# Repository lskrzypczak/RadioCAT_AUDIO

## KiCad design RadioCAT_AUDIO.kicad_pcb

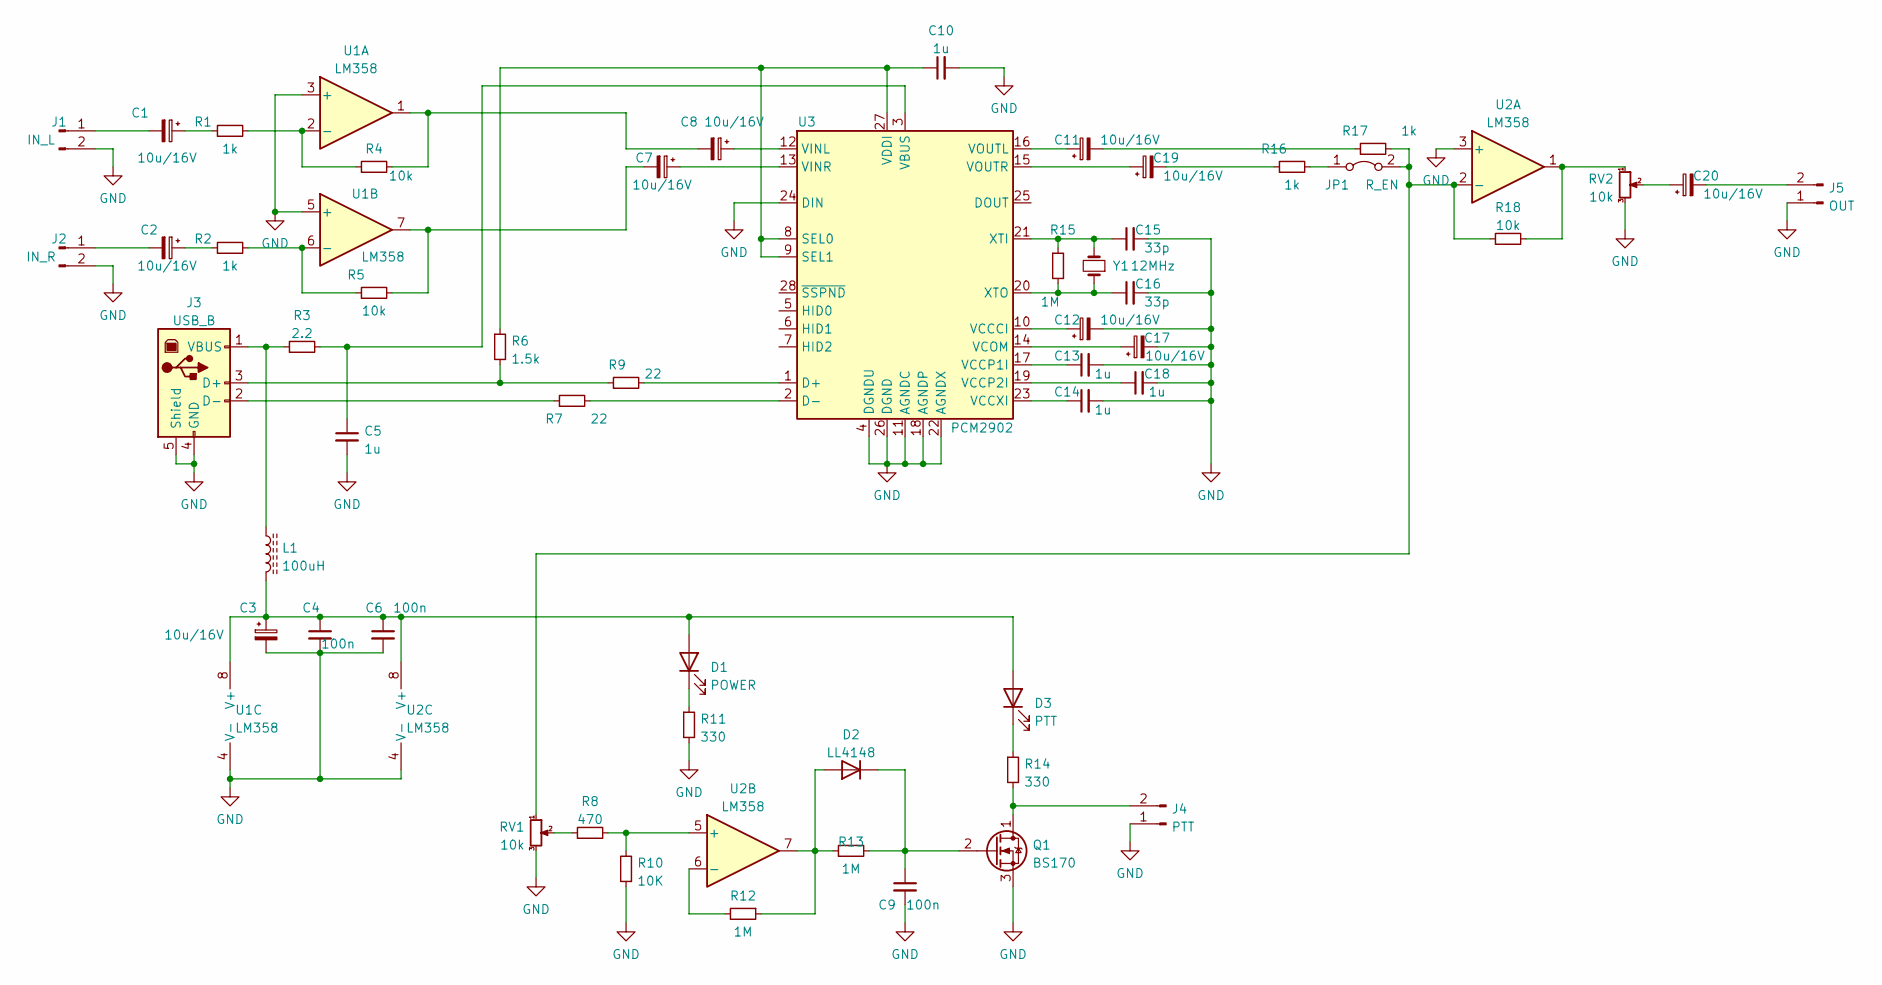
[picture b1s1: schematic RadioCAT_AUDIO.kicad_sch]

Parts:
C1, C2, C3, C7, C8, C11, C12, C17, C19, C20: 10u/16V; CP_Radial_D5.0mm_P2.50mm
C4, C6, C9: 100n; R_0805_2012Metric_Pad1.20x1.40mm_HandSolder
C5, C10, C13, C14, C18: 1u; R_0805_2012Metric_Pad1.20x1.40mm_HandSolder
C15, C16: 33p; R_0805_2012Metric_Pad1.20x1.40mm_HandSolder
D1: POWER; PinHeader_1x02_P2.54mm_Vertical
D2: LL4148; D_MiniMELF
D3: PTT; PinHeader_1x02_P2.54mm_Vertical
J1: IN_L; PinHeader_1x02_P2.54mm_Vertical
J2: IN_R; PinHeader_1x02_P2.54mm_Vertical
J3: USB_B; USB_B_Lumberg_2411_02_Horizontal
J4: PTT; PinHeader_1x02_P2.54mm_Vertical
J5: OUT; PinHeader_1x02_P2.54mm_Vertical
JP1: R_EN; PinHeader_1x02_P2.54mm_Vertical
L1: 100uH; L_7.3x7.3_H4.5
Q1: BS170; TO-92_Inline
R1, R2, R16, R17: 1k; R_0805_2012Metric_Pad1.20x1.40mm_HandSolder
R3: 2.2; R_0805_2012Metric_Pad1.20x1.40mm_HandSolder
R4, R5, R18: 10k; R_0805_2012Metric_Pad1.20x1.40mm_HandSolder
R6: 1.5k; R_0805_2012Metric_Pad1.20x1.40mm_HandSolder
R7, R9: 22; R_0805_2012Metric_Pad1.20x1.40mm_HandSolder
R8: 470; R_0805_2012Metric_Pad1.20x1.40mm_HandSolder
R10: 10K; R_0805_2012Metric_Pad1.20x1.40mm_HandSolder
R11, R14: 330; R_0805_2012Metric_Pad1.20x1.40mm_HandSolder
R12, R13, R15: 1M; R_0805_2012Metric_Pad1.20x1.40mm_HandSolder
RV1, RV2: 10k; PinHeader_1x03_P2.54mm_Vertical
U1, U2: LM358; SO-8_3.9x4.9mm_P1.27mm
U3: PCM2902; SSOP-28_5.3x10.2mm_P0.65mm
Y1: 12MHz; Crystal_HC49-4H_Vertical

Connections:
GND: C3.2, C4.2, C5.2, C6.2, C9.2, C10.2, C12.2, C13.2, C14.2, C15.2, C16.2, C17.2, C18.2, J1.2, J2.2, J3.4 (GND), J3.5 (Shield), J4.1, J5.1, Q1.3 (S), R10.1, R11.2, RV1.3, RV2.3, U1.3 (+), U1.4 (V-), U1.5 (+), U2.3 (+), U2.4 (V-), U3.4 (DGNDU), U3.11 (AGNDC), U3.18 (AGNDP), U3.22 (AGNDX), U3.24 (DIN), U3.26 (DGND)
unnamed: C1.1, R1.1
unnamed: C1.2, J1.1
unnamed: C2.1, R2.1
unnamed: C2.2, J2.1
unnamed: C3.1, C4.1, C6.1, D1.2 (A), D3.2 (A), L1.2, U1.8 (V+), U2.8 (V+)
unnamed: C5.1, R3.2, U3.3 (VBUS)
unnamed: C7.1, U3.13 (VINR)
unnamed: C7.2, R5.2, U1.7
unnamed: C8.1, U3.12 (VINL)
unnamed: C8.2, R4.2, U1.1
unnamed: C9.1, D2.1 (K), Q1.2 (G), R13.2
unnamed: C10.1, R6.1, U3.8 (SEL0), U3.9 (SEL1), U3.27 (VDDI)
unnamed: C11.1, U3.16 (VOUTL)
unnamed: C11.2, R17.1
unnamed: C12.1, U3.10 (VCCCI)
unnamed: C13.1, U3.17 (VCCP1I)
unnamed: C14.1, U3.23 (VCCXI)
unnamed: C15.1, R15.1, U3.21 (XTI), Y1.2
unnamed: C16.1, R15.2, U3.20 (XTO), Y1.1
unnamed: C17.1, U3.14 (VCOM)
unnamed: C18.1, U3.19 (VCCP2I)
unnamed: C19.1, U3.15 (VOUTR)
unnamed: C19.2, R16.1
unnamed: C20.1, RV2.2
unnamed: C20.2, J5.2
unnamed: D1.1 (K), R11.1
unnamed: D2.2 (A), R12.1, R13.1, U2.7
unnamed: D3.1 (K), R14.1
unnamed: J3.1 (VBUS), L1.1, R3.1
unnamed: J3.2 (D-), R7.1
unnamed: J3.3 (D+), R6.2, R9.1
unnamed: J4.2, Q1.1 (D), R14.2
unnamed: JP1.1 (A), R16.2
unnamed: JP1.2 (B), R17.2, R18.1, RV1.1, U2.2 (-)
unnamed: R1.2, R4.1, U1.2 (-)
unnamed: R2.2, R5.1, U1.6 (-)
unnamed: R7.2, U3.2 (D-)
unnamed: R8.1, RV1.2
unnamed: R9.2, U3.1 (D+)
unnamed: R8.2, R10.2, U2.5 (+)
unnamed: R12.2, U2.6 (-)
unnamed: R18.2, RV2.1, U2.1

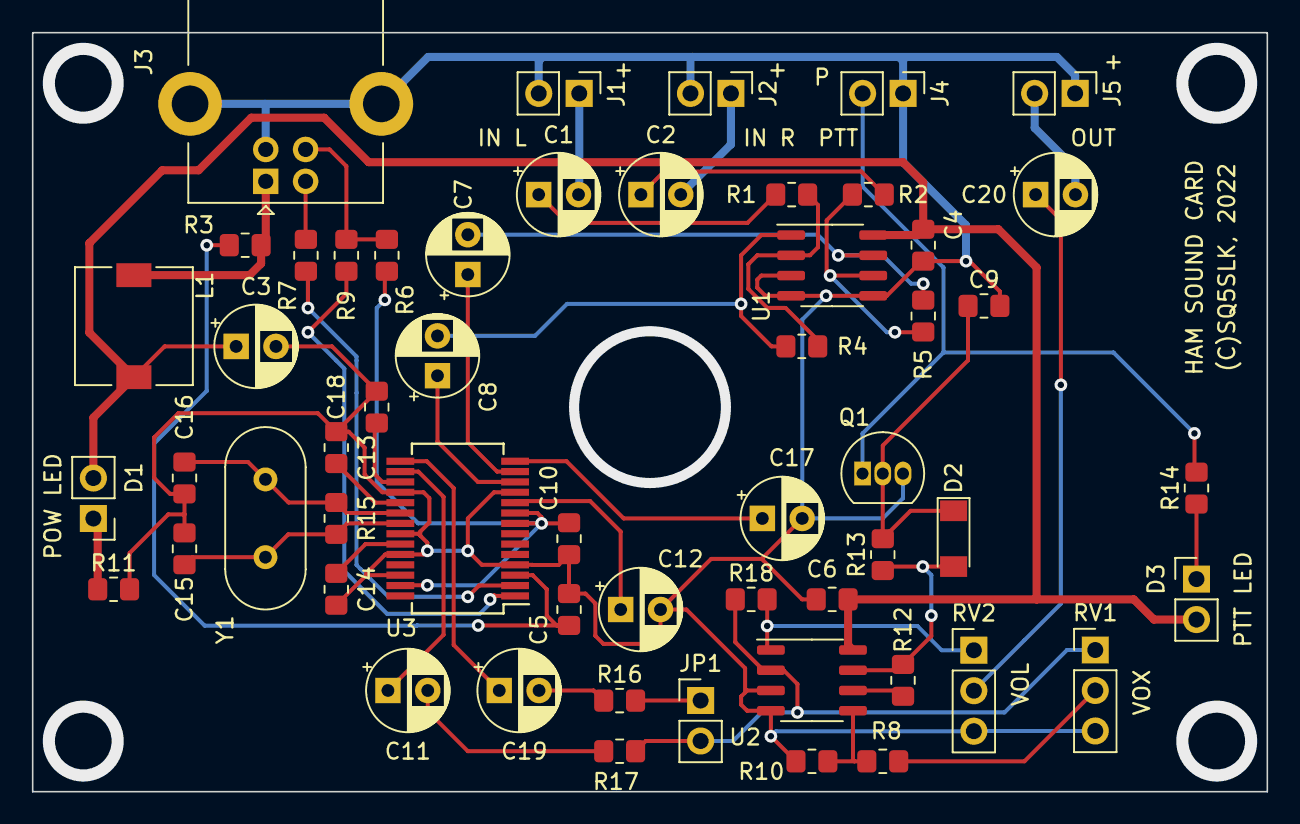
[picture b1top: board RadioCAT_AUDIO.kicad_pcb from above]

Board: 2 copper layers, 77.5 x 47.6 mm, 55 parts (0 on the bottom side), 43 nets.
